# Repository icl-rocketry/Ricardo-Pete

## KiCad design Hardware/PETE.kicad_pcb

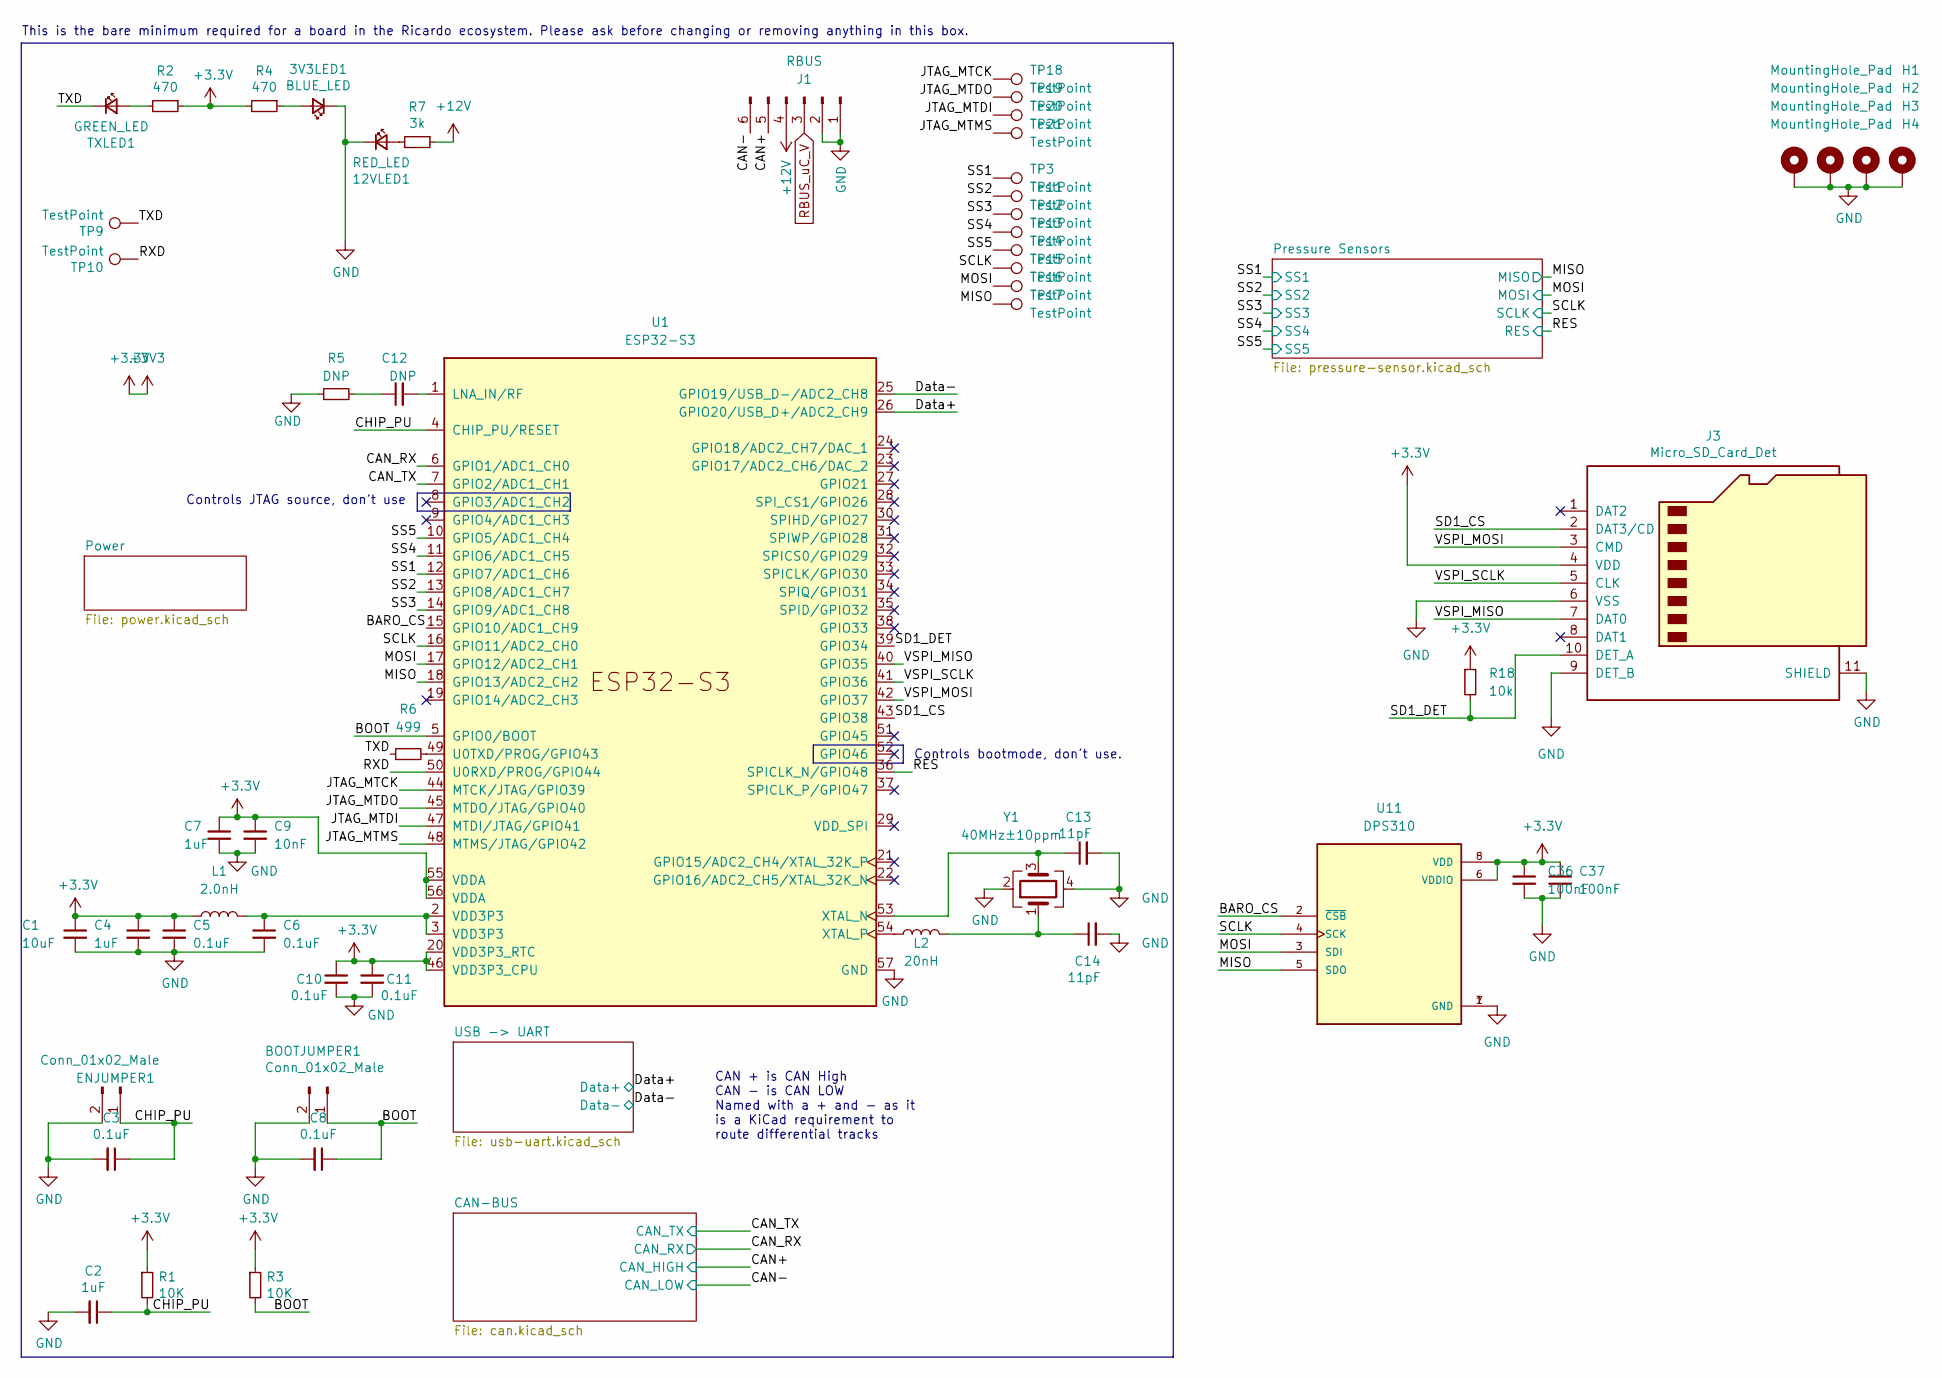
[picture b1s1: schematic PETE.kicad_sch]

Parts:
3V3LED1: BLUE_LED; R_0402_1005Metric
12VLED1: RED_LED; R_0402_1005Metric
BOOTJUMPER1: Conn_01x02_Male; PinHeader_1x02_P2.54mm_Vertical
C1: 10uF; C_0402_1005Metric
C2, C4, C7: 1uF; C_0402_1005Metric
C3, C5, C6, C8, C10, C11: 0.1uF; C_0402_1005Metric
C9: 10nF; C_0402_1005Metric
C12: DNP; C_0402_1005Metric
C13, C14: 11pF; C_0402_1005Metric
C36, C37: 100nF; C_0402_1005Metric
ENJUMPER1: Conn_01x02_Male; PinHeader_1x02_P2.54mm_Vertical
H1, H2, H3, H4: MountingHole_Pad; MountingHole_3.2mm_M3_DIN965_Pad
J1: RBUS; Molex_Mini-Fit_Jr_5566-06A_2x03_P4.20mm_Vertical
J3: Micro_SD_Card_Det; microSD_HC_Hirose_DM3AT-SF-PEJM5
L1: 2.0nH; L_0402_1005Metric
L2: 20nH; L_0402_1005Metric
R1, R3: 10K; R_0402_1005Metric
R2, R4: 470; R_0402_1005Metric
R5: DNP; R_0402_1005Metric
R6: 499; R_0402_1005Metric
R7: 3k; R_0402_1005Metric
R18: 10k; R_0402_1005Metric
TP3, TP9, TP10, TP11, TP12, TP13, TP14, TP15, TP16, TP17, TP18, TP19, TP20, TP21: TestPoint; TestPoint_Pad_D1.0mm
TXLED1: GREEN_LED; R_0402_1005Metric
U1: ESP32-S3; QFN40P700X700X90-57N
U11: DPS310; XDCR_DPS310
Y1: 40MHz±10ppm; Crystal_SMD_2016-4Pin_2.0x1.6mm

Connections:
+3.3V: C1.1, C4.1, C5.1, C7.1, C9.1, C10.1, C11.1, C36.1, C37.1, J3.4 (VDD), L1.1, R1.1, R2.1, R3.1, R4.2, R18.1, U1.20 (VDD3P3_RTC), U1.46 (VDD3P3_CPU), U1.55 (VDDA), U1.56 (VDDA), U11.6 (VDDIO), U11.8 (VDD); also elsewhere on the board
+12V: J1.4, R7.1
/BARO_CS: U1.15 (GPIO10/ADC1_CH9), U11.2 (~CSB)
/BOOT: BOOTJUMPER1.1, C8.1, R3.2, U1.5 (GPIO0/BOOT)
/CAN+: J1.5; also elsewhere on the board
/CAN-: J1.6; also elsewhere on the board
/CAN_RX: U1.6 (GPIO1/ADC1_CH0); also elsewhere on the board
/CAN_TX: U1.7 (GPIO2/ADC1_CH1); also elsewhere on the board
/CHIP_PU: C2.1, C3.1, ENJUMPER1.1, R1.2, U1.4 (CHIP_PU/RESET)
/Data+: U1.26 (GPIO20/USB_D+/ADC2_CH9); also elsewhere on the board
/Data-: U1.25 (GPIO19/USB_D-/ADC2_CH8); also elsewhere on the board
/JTAG_MTCK: TP18.1, U1.44 (MTCK/JTAG/GPIO39)
/JTAG_MTDI: TP20.1, U1.47 (MTDI/JTAG/GPIO41)
/JTAG_MTDO: TP19.1, U1.45 (MTDO/JTAG/GPIO40)
/JTAG_MTMS: TP21.1, U1.48 (MTMS/JTAG/GPIO42)
/MISO: TP17.1, U1.18 (GPIO13/ADC2_CH2), U11.5 (SDO); also elsewhere on the board
/MOSI: TP16.1, U1.17 (GPIO12/ADC2_CH1), U11.3 (SDI); also elsewhere on the board
/RES: U1.36 (SPICLK_N/GPIO48); also elsewhere on the board
/RXD: TP10.1, U1.50 (U0RXD/PROG/GPIO44)
/SCLK: TP15.1, U1.16 (GPIO11/ADC2_CH0), U11.4 (SCK); also elsewhere on the board
/SD1_CS: J3.2 (DAT3/CD), U1.43 (GPIO38)
/SD1_DET: J3.10 (DET_A), R18.2, U1.39 (GPIO34)
/SS1: TP3.1, U1.12 (GPIO7/ADC1_CH6); also elsewhere on the board
/SS2: TP11.1, U1.13 (GPIO8/ADC1_CH7); also elsewhere on the board
/SS3: TP12.1, U1.14 (GPIO9/ADC1_CH8); also elsewhere on the board
/SS4: TP13.1, U1.11 (GPIO6/ADC1_CH5); also elsewhere on the board
/SS5: TP14.1, U1.10 (GPIO5/ADC1_CH4); also elsewhere on the board
/TXD: R6.1, TP9.1, TXLED1.1 (K)
/VSPI_MISO: J3.7 (DAT0), U1.40 (GPIO35)
/VSPI_MOSI: J3.3 (CMD), U1.42 (GPIO37)
/VSPI_SCLK: J3.5 (CLK), U1.41 (GPIO36)
GND: 3V3LED1.1 (K), 12VLED1.1 (K), BOOTJUMPER1.2, C1.2, C2.2, C3.2, C4.2, C5.2, C6.2, C7.2, C8.2, C9.2, C10.2, C11.2, C13.2, C14.2, C36.2, C37.2, ENJUMPER1.2, H1.1, H2.1, H3.1, H4.1, J1.1, J1.2, J3.6 (VSS), J3.9 (DET_B), J3.11 (SHIELD), R5.1, U1.57 (GND), U11.1 (GND), U11.7 (GND), Y1.2, Y1.4; also elsewhere on the board
unnamed: 3V3LED1.2 (A), R4.1
unnamed: 12VLED1.2 (A), R7.2
unnamed: C6.1, L1.2, U1.2 (VDD3P3), U1.3 (VDD3P3)
unnamed: C12.1, R5.2
unnamed: C14.1, L2.2, Y1.1
unnamed: R2.2, TXLED1.2 (A)
unnamed: C12.2, U1.1 (LNA_IN/RF)
unnamed: R6.2, U1.49 (U0TXD/PROG/GPIO43)
unnamed: C13.1, U1.53 (XTAL_N), Y1.3
unnamed: L2.1, U1.54 (XTAL_P)
RBUS_uC_V: J1.3; also elsewhere on the board

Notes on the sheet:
Controls bootmode, don't use.
This is the bare minimum required for a board in the Ricardo ecosystem. Please ask before changing or removing anything in this box.
CAN + is CAN High CAN - is CAN LOW Named with a + and - as it is a KiCad requirement to route differential tracks
Controls JTAG source, don't use

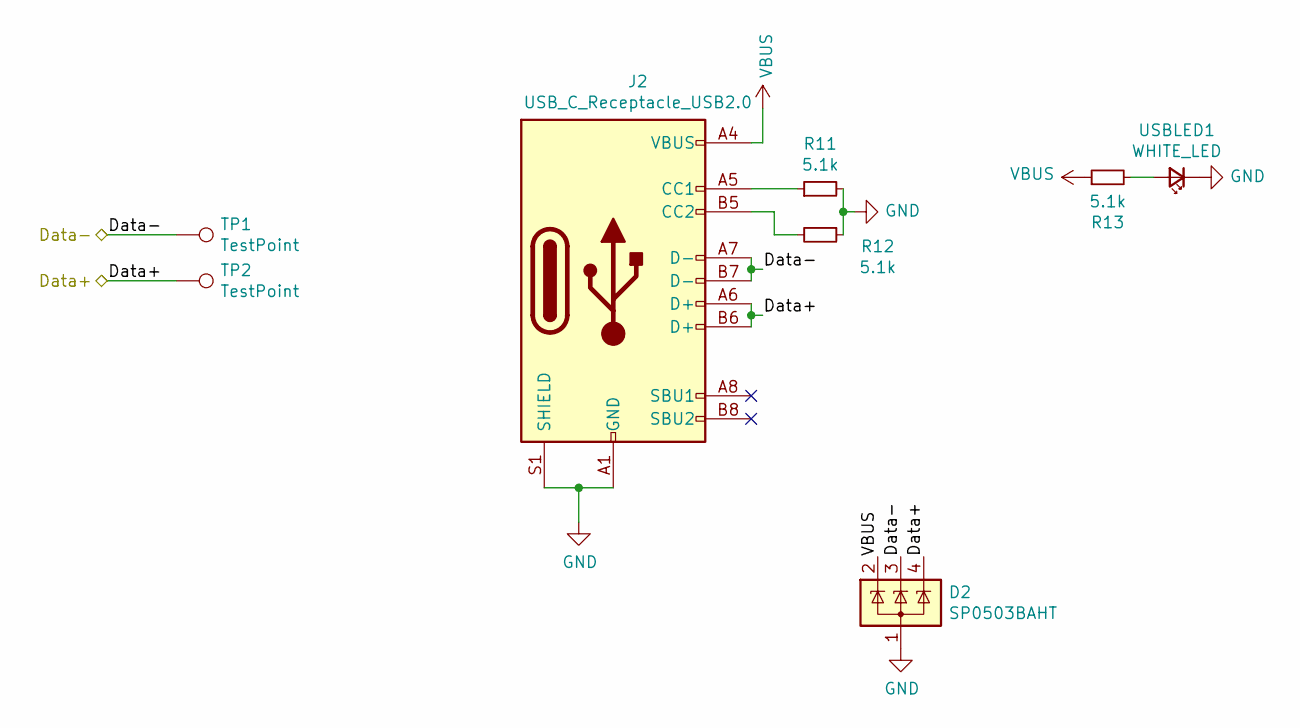
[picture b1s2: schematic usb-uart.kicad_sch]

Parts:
D2: SP0503BAHT; SOT-143
J2: USB_C_Receptacle_USB2.0; USB_C_Receptacle_Palconn_UTC16-G
R11, R12, R13: 5.1k; R_0402_1005Metric
TP1, TP2: TestPoint; TestPoint_Pad_D1.0mm
USBLED1: WHITE_LED; R_0402_1005Metric

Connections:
/Data+: D2.4 (K), J2.A6 (D+), J2.B6 (D+), TP2.1; also elsewhere on the board
/Data-: D2.3 (K), J2.A7 (D-), J2.B7 (D-), TP1.1; also elsewhere on the board
GND: D2.1 (A), J2.A1 (GND), J2.A12 (GND), J2.B1 (GND), J2.B12 (GND), J2.S1 (SHIELD), R11.2, R12.1, USBLED1.1 (K); also elsewhere on the board
unnamed: J2.A5 (CC1), R11.1
unnamed: J2.B5 (CC2), R12.2
unnamed: R13.2, USBLED1.2 (A)
VBUS: D2.2 (K), J2.A4 (VBUS), J2.A9 (VBUS), J2.B4 (VBUS), J2.B9 (VBUS), R13.1; also elsewhere on the board

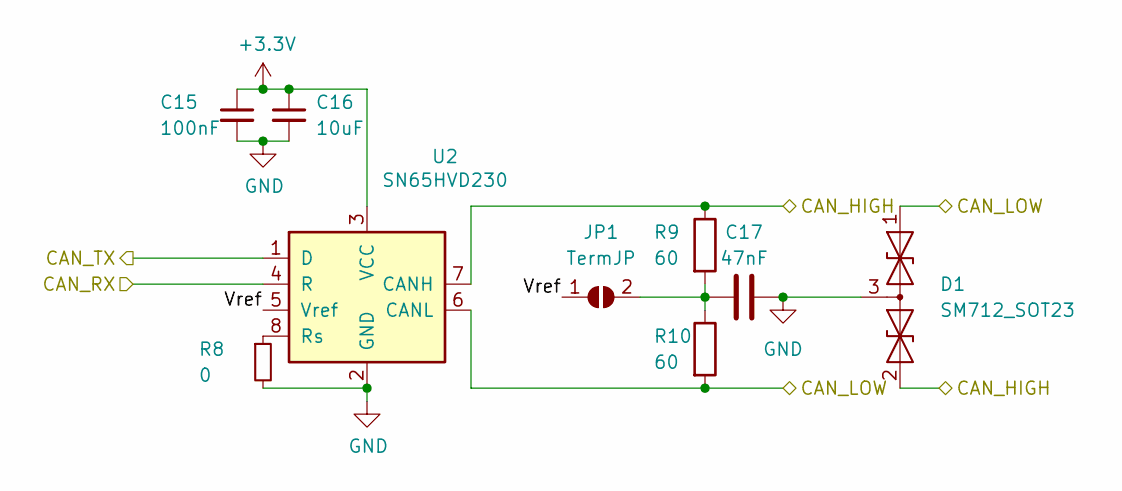
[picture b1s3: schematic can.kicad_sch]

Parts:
C15: 100nF; C_0402_1005Metric
C16: 10uF; C_0402_1005Metric
C17: 47nF; C_0402_1005Metric
D1: SM712_SOT23; SOT-23
JP1: TermJP; SolderJumper-2_P1.3mm_Open_RoundedPad1.0x1.5mm
R8: 0; R_0603_1608Metric
R9, R10: 60; R_0603_1608Metric
U2: SN65HVD230; SOIC-8_3.9x4.9mm_P1.27mm

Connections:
+3.3V: C15.1, C16.1, U2.3 (VCC); also elsewhere on the board
/CAN+: D1.2 (A2), R9.1, U2.7 (CANH); also elsewhere on the board
/CAN-: D1.1 (A1), R10.2, U2.6 (CANL); also elsewhere on the board
/CAN-BUS/Vref: JP1.1 (A), U2.5 (Vref)
/CAN_RX: U2.4 (R); also elsewhere on the board
/CAN_TX: U2.1 (D); also elsewhere on the board
GND: C15.2, C16.2, C17.2, D1.3 (common), R8.2, U2.2 (GND); also elsewhere on the board
unnamed: C17.1, JP1.2 (B), R9.2, R10.1
unnamed: R8.1, U2.8 (Rs)

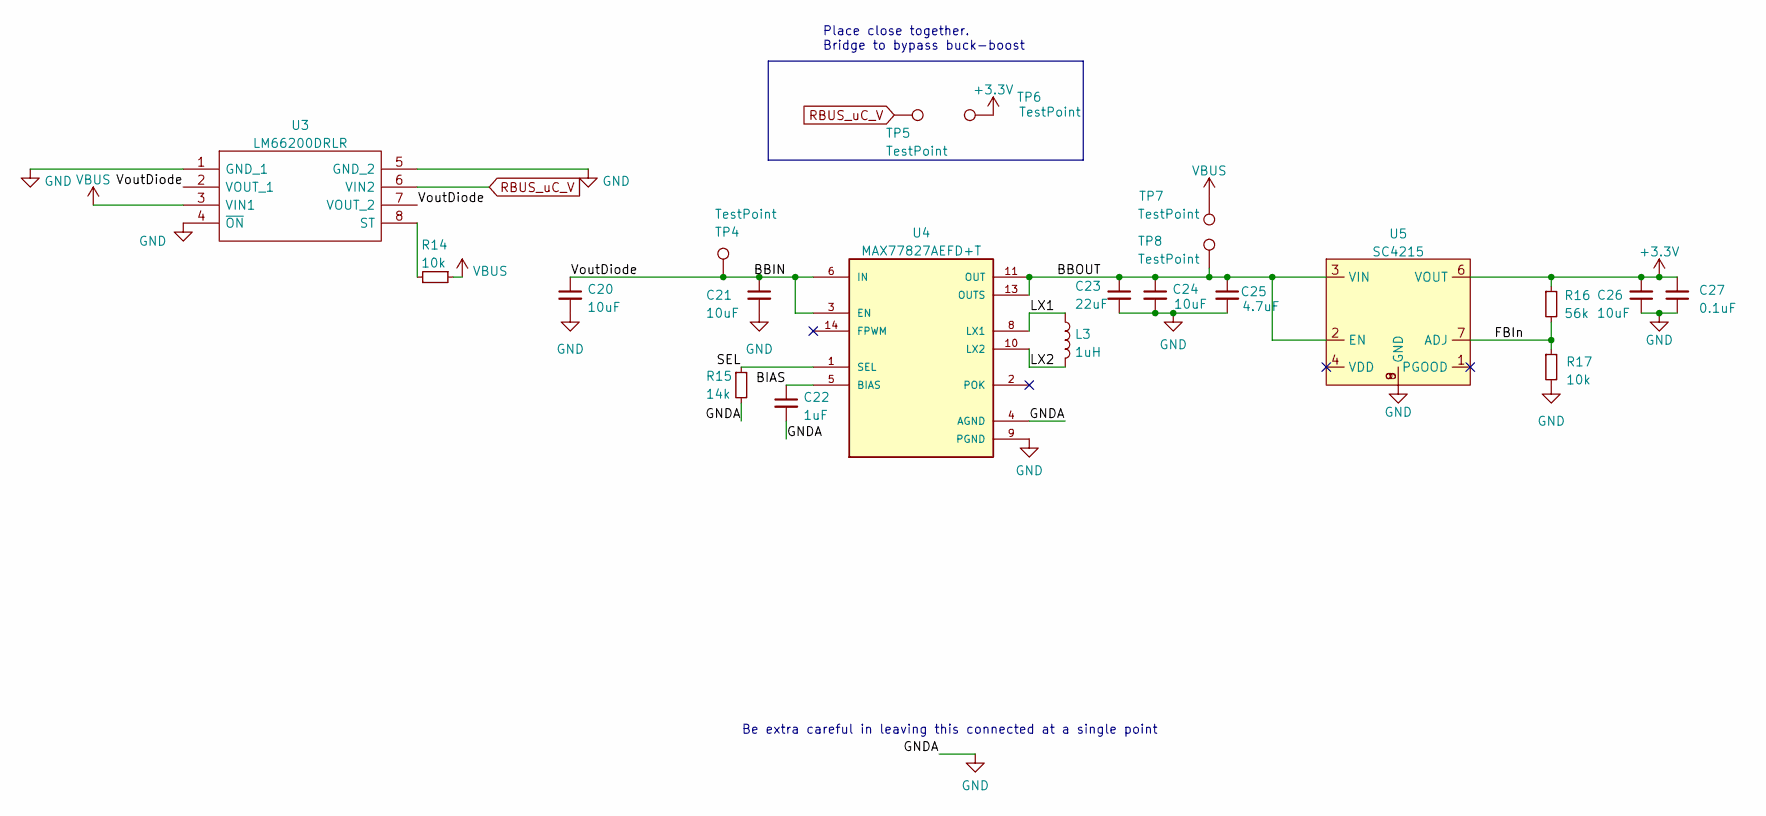
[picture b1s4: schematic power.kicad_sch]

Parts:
C20, C24, C26: 10uF; C_0402_1005Metric
C21: 10uF; C_0603_1608Metric
C22: 1uF; C_0402_1005Metric
C23: 22uF; C_0603_1608Metric
C25: 4.7uF; C_0402_1005Metric
C27: 0.1uF; C_0402_1005Metric
L3: 1uH; L_0805_2012Metric
R14, R17: 10k; R_0402_1005Metric
R15: 14k; R_0402_1005Metric
R16: 56k; R_0402_1005Metric
TP4, TP5, TP6, TP7, TP8: TestPoint; TestPoint_Pad_D1.0mm
U3: LM66200DRLR; SOTFL50P160X60-8N; Manufacturer_Part_Number LM66200DRLR; Mouser Part Number 595-LM66200DRLR
U4: MAX77827AEFD+T; CONV_MAX77827AEFD+T; PARTREV B
U5: SC4215; SOIC127P599X175-9N

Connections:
+3.3V: C26.2, C27.2, R16.1, TP6.1, U5.6 (VOUT); also elsewhere on the board
/Power/BBIN: C20.1, C21.1, TP4.1, U3.2 (VOUT_1), U3.7 (VOUT_2), U4.3 (EN), U4.6 (IN)
/Power/BBOUT: C23.1, C24.1, C25.1, TP8.1, U4.11 (OUT), U4.13 (OUTS), U5.2 (EN), U5.3 (VIN)
/Power/BIAS: C22.1, U4.5 (BIAS)
/Power/FBIn: R16.2, R17.1, U5.7 (ADJ)
/Power/LX1: L3.1, U4.8 (LX1)
/Power/LX2: L3.2, U4.10 (LX2)
/Power/SEL: R15.1, U4.1 (SEL)
GND: C20.2, C21.2, C22.2, C23.2, C24.2, C25.2, C26.1, C27.1, R15.2, R17.2, U3.1 (GND_1), U3.4 (~ON), U3.5 (GND_2), U4.4 (AGND), U4.9 (PGND), U5.8 (GND), U5.9 (GND); also elsewhere on the board
unnamed: R14.2, U3.8 (ST)
RBUS_uC_V: TP5.1, U3.6 (VIN2); also elsewhere on the board
VBUS: R14.1, TP7.1, U3.3 (VIN1); also elsewhere on the board

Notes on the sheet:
Place close together. Bridge to bypass buck-boost
Be extra careful in leaving this connected at a single point

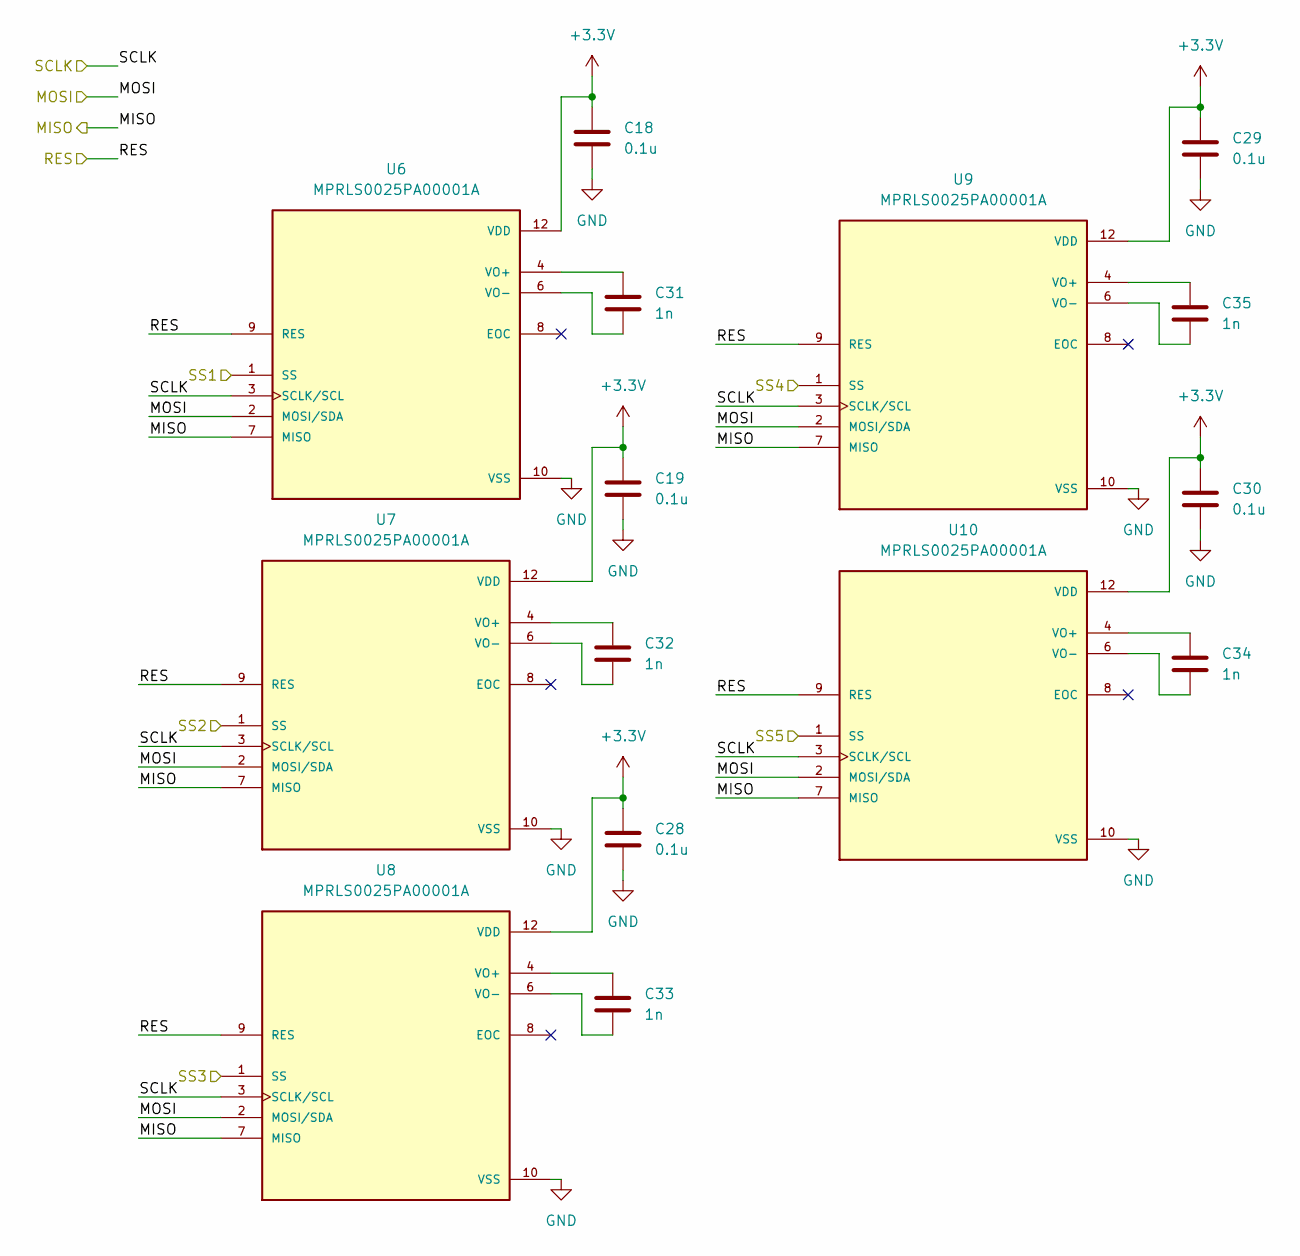
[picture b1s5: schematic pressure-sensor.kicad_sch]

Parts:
C18, C19, C28, C29, C30: 0.1u; C_0402_1005Metric
C31, C32, C33, C34, C35: 1n; C_0402_1005Metric
U6, U7, U8, U9, U10: MPRLS0025PA00001A; XDCR_MPRLS0025PA00001A; PARTREV 03/18

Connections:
+3.3V: C18.1, C19.1, C28.1, C29.1, C30.1, U6.12 (VDD), U7.12 (VDD), U8.12 (VDD), U9.12 (VDD), U10.12 (VDD); also elsewhere on the board
/MISO: U6.7 (MISO), U7.7 (MISO), U8.7 (MISO), U9.7 (MISO), U10.7 (MISO); also elsewhere on the board
/MOSI: U6.2 (MOSI/SDA), U7.2 (MOSI/SDA), U8.2 (MOSI/SDA), U9.2 (MOSI/SDA), U10.2 (MOSI/SDA); also elsewhere on the board
/RES: U6.9 (RES), U7.9 (RES), U8.9 (RES), U9.9 (RES), U10.9 (RES); also elsewhere on the board
/SCLK: U6.3 (SCLK/SCL), U7.3 (SCLK/SCL), U8.3 (SCLK/SCL), U9.3 (SCLK/SCL), U10.3 (SCLK/SCL); also elsewhere on the board
/SS1: U6.1 (SS); also elsewhere on the board
/SS2: U7.1 (SS); also elsewhere on the board
/SS3: U8.1 (SS); also elsewhere on the board
/SS4: U9.1 (SS); also elsewhere on the board
/SS5: U10.1 (SS); also elsewhere on the board
GND: C18.2, C19.2, C28.2, C29.2, C30.2, U6.10 (VSS), U7.10 (VSS), U8.10 (VSS), U9.10 (VSS), U10.10 (VSS); also elsewhere on the board
unnamed: C31.1, U6.4 (VO+)
unnamed: C31.2, U6.6 (VO-)
unnamed: C32.1, U7.4 (VO+)
unnamed: C32.2, U7.6 (VO-)
unnamed: C33.1, U8.4 (VO+)
unnamed: C33.2, U8.6 (VO-)
unnamed: C35.1, U9.4 (VO+)
unnamed: C35.2, U9.6 (VO-)
unnamed: C34.1, U10.4 (VO+)
unnamed: C34.2, U10.6 (VO-)

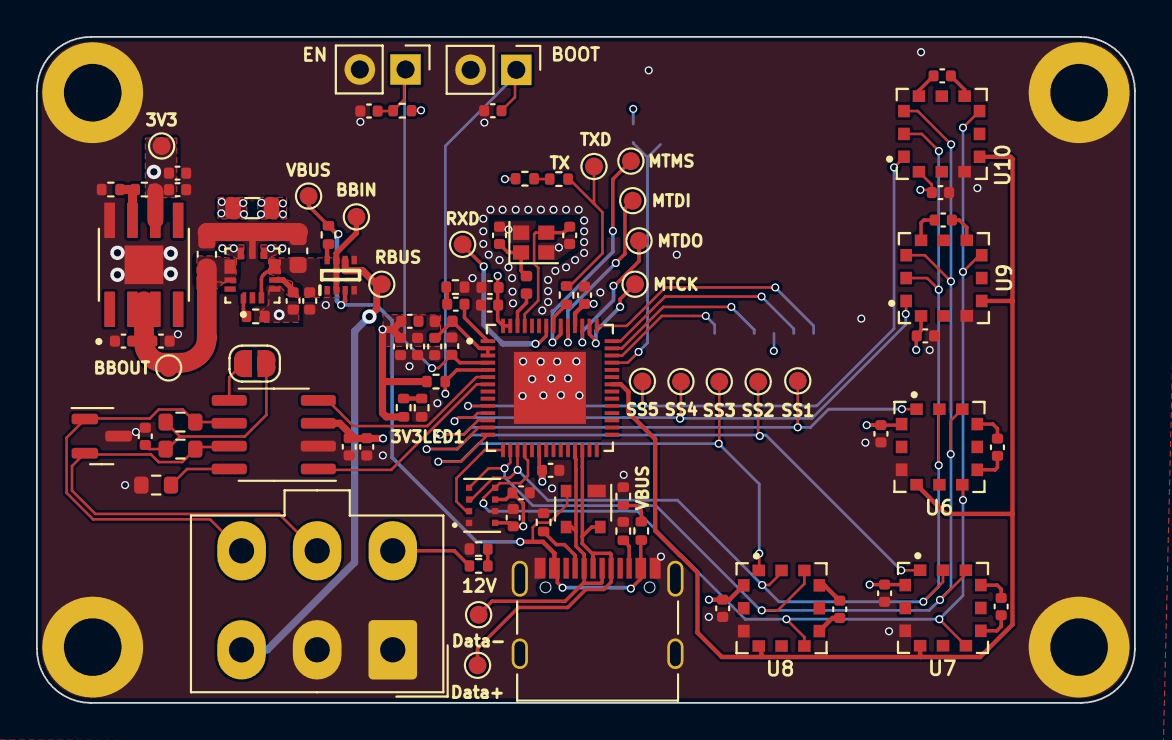
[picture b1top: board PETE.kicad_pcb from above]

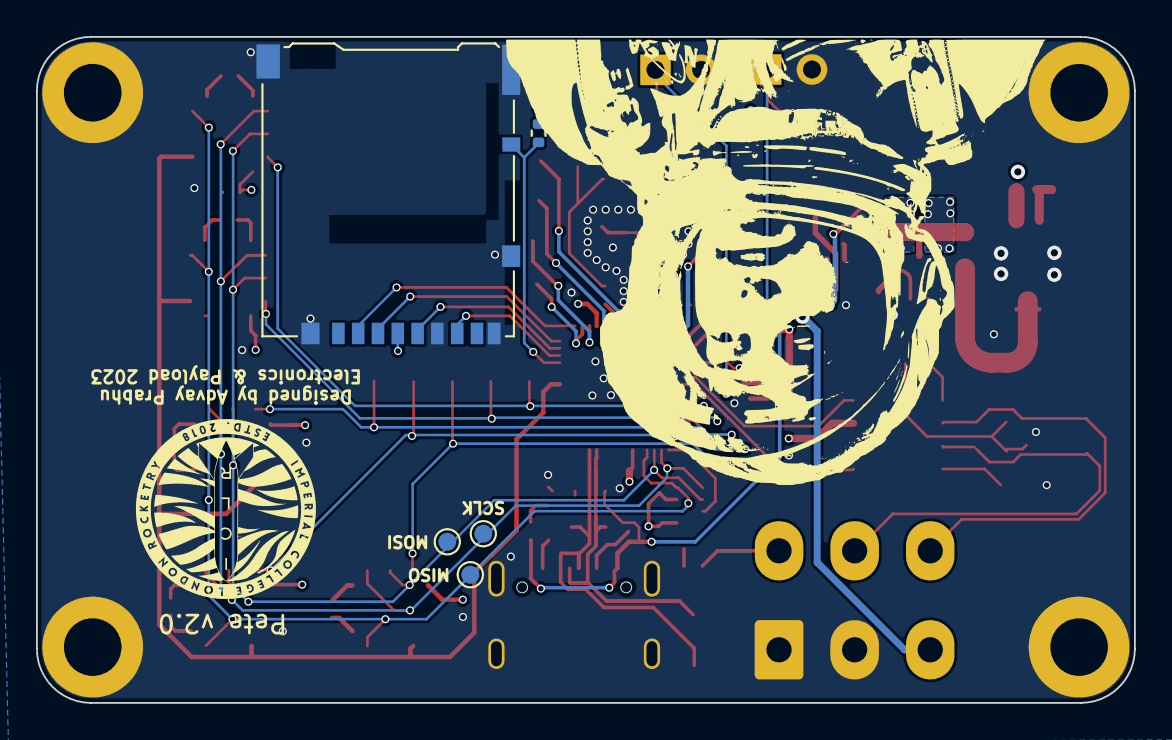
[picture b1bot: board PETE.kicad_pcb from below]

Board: 4 copper layers, 61.0 x 37.0 mm, 107 parts (5 on the bottom side), 68 nets.

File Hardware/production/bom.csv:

Designator,Footprint,Quantity,Value,LCSC Part #
12VLED1,0402,1,RED_LED,
3V3LED1,0402,1,BLUE_LED,
"BOOTJUMPER1, ENJUMPER1",PinHeader_1x02_P2.54mm_Vertical,2,Conn_01x02_Male,
"C1, C16, C20, C24, C26",0402,5,10uF,
"C10, C11, C27, C3, C5, C6, C8",0402,7,0.1uF,
"C12, R5",0402,2,DNP,
"C13, C14",0402,2,11pF,
"C15, C36, C37",0402,3,100nF,
C17,0402,1,47nF,
"C18, C19, C28, C29, C30",0402,5,0.1u,
"C2, C22, C4, C7",0402,4,1uF,
C21,0603,1,10uF,
C23,0603,1,22uF,
C25,0402,1,4.7uF,
"C31, C32, C33, C34, C35",0402,5,1n,
C9,0402,1,10nF,
D1,SOT-23,1,SM712_SOT23,
D2,SOT-143,1,SP0503BAHT,
"H1, H2, H3, H4",MountingHole_3.2mm_M3_DIN965_Pad,4,MountingHole_Pad,
J1,Molex_Mini-Fit_Jr_5566-06A_2x03_P4.20mm_Vertical,1,RBUS,
J2,USB_C_Receptacle_Palconn_UTC16-G,1,USB_C_Receptacle_USB2.0,
J3,microSD_HC_Hirose_DM3AT-SF-PEJM5,1,Micro_SD_Card_Det,
JP1,SolderJumper-2_P1.3mm_Open_RoundedPad1.0x1.5mm,1,TermJP,
L1,0402,1,2.0nH,
L2,0402,1,20nH,
L3,0805,1,1uH,
"R1, R14, R17, R18, R3",0402,5,10K,
"R10, R9",0603,2,60,
"R11, R12, R13",0402,3,5.1k,
R15,0402,1,14k,
R16,0402,1,56k,
"R2, R4",0402,2,470,
R6,0402,1,499,
R7,0402,1,3k,
R8,0603,1,0,
"TP1, TP10, TP11, TP12, TP13, TP14, TP15, TP16, TP17, TP18, TP19, TP2, TP20, TP21, TP3, TP4, TP5, TP6, TP7, TP8, TP9",TestPoint_Pad_D1.0mm,21,TestPoint,
TXLED1,0402,1,GREEN_LED,
U1,QFN40P700X700X90-57N,1,ESP32-S3,
"U10, U6, U7, U8, U9",XDCR_MPRLS0025PA00001A,5,MPRLS0025PA00001A,
U11,XDCR_DPS310,1,DPS310,
U2,SOIC-8_3.9x4.9mm_P1.27mm,1,SN65HVD230,
U3,SOTFL50P160X60-8N,1,LM66200DRLR,
U4,CONV_MAX77827AEFD+T,1,MAX77827AEFD+T,
U5,SOIC127P599X175-9N,1,SC4215,
USBLED1,0402,1,WHITE_LED,
Y1,Crystal_SMD_2016-4Pin_2.0x1.6mm,1,40MHz±10ppm,

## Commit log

2023-08-09 Schematic
2023-08-17 PCB Done
2023-08-19 Review Changes Made (except for meme)
2023-08-20 Review Changes
    Still don't know whats going on with the overlapping pours. Meme is a bit rubbish but it'll do for now.
2023-08-23 More Review Changes
    Issue with overlapping pours not fixed yet.
2023-08-23 artem review
2023-08-25 forgot name of board + some missed drc
2023-09-05 ordering
2023-09-14 Pressure Sensor Driver
2023-10-05 firmware
2023-12-02 updated arduino submodule to corrrect version
2024-07-20 repairing repo
2024-07-20 fixed git issues
